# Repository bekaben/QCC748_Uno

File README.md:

# Arduino Uno Compatible Board Based on Qualcomm QCC748 SOM

<br>

<br>

This is a custom Arduino Uno-compatible board built around the Qualcomm QCC748 System-on-Module (SOM). This repository contains the full schematic, PCB layout, and supporting documentation for the board design.

## 🔧 Overview

This project implements an Arduino Uno form-factor development board using the Qualcomm QCC748 SOM as the core processing module. The design maintains compatibility with the Arduino Uno pinout while leveraging the QCC748's capabilities for enhanced wireless connectivity and processing performance. In addition, the board includes a speaker, microphone, and MicroSD card interface.

## Key Goals

\- ✅ Arduino Uno R3 mechanical footprint compatibility

\- ✅ Standard Arduino header pinout

\- ✅ USB programming interface

\- ✅ Power supply regulation (5V / 3.3V)

\- ✅ Wireless connectivity via QCC748 integrated Wifi and Bluetooth

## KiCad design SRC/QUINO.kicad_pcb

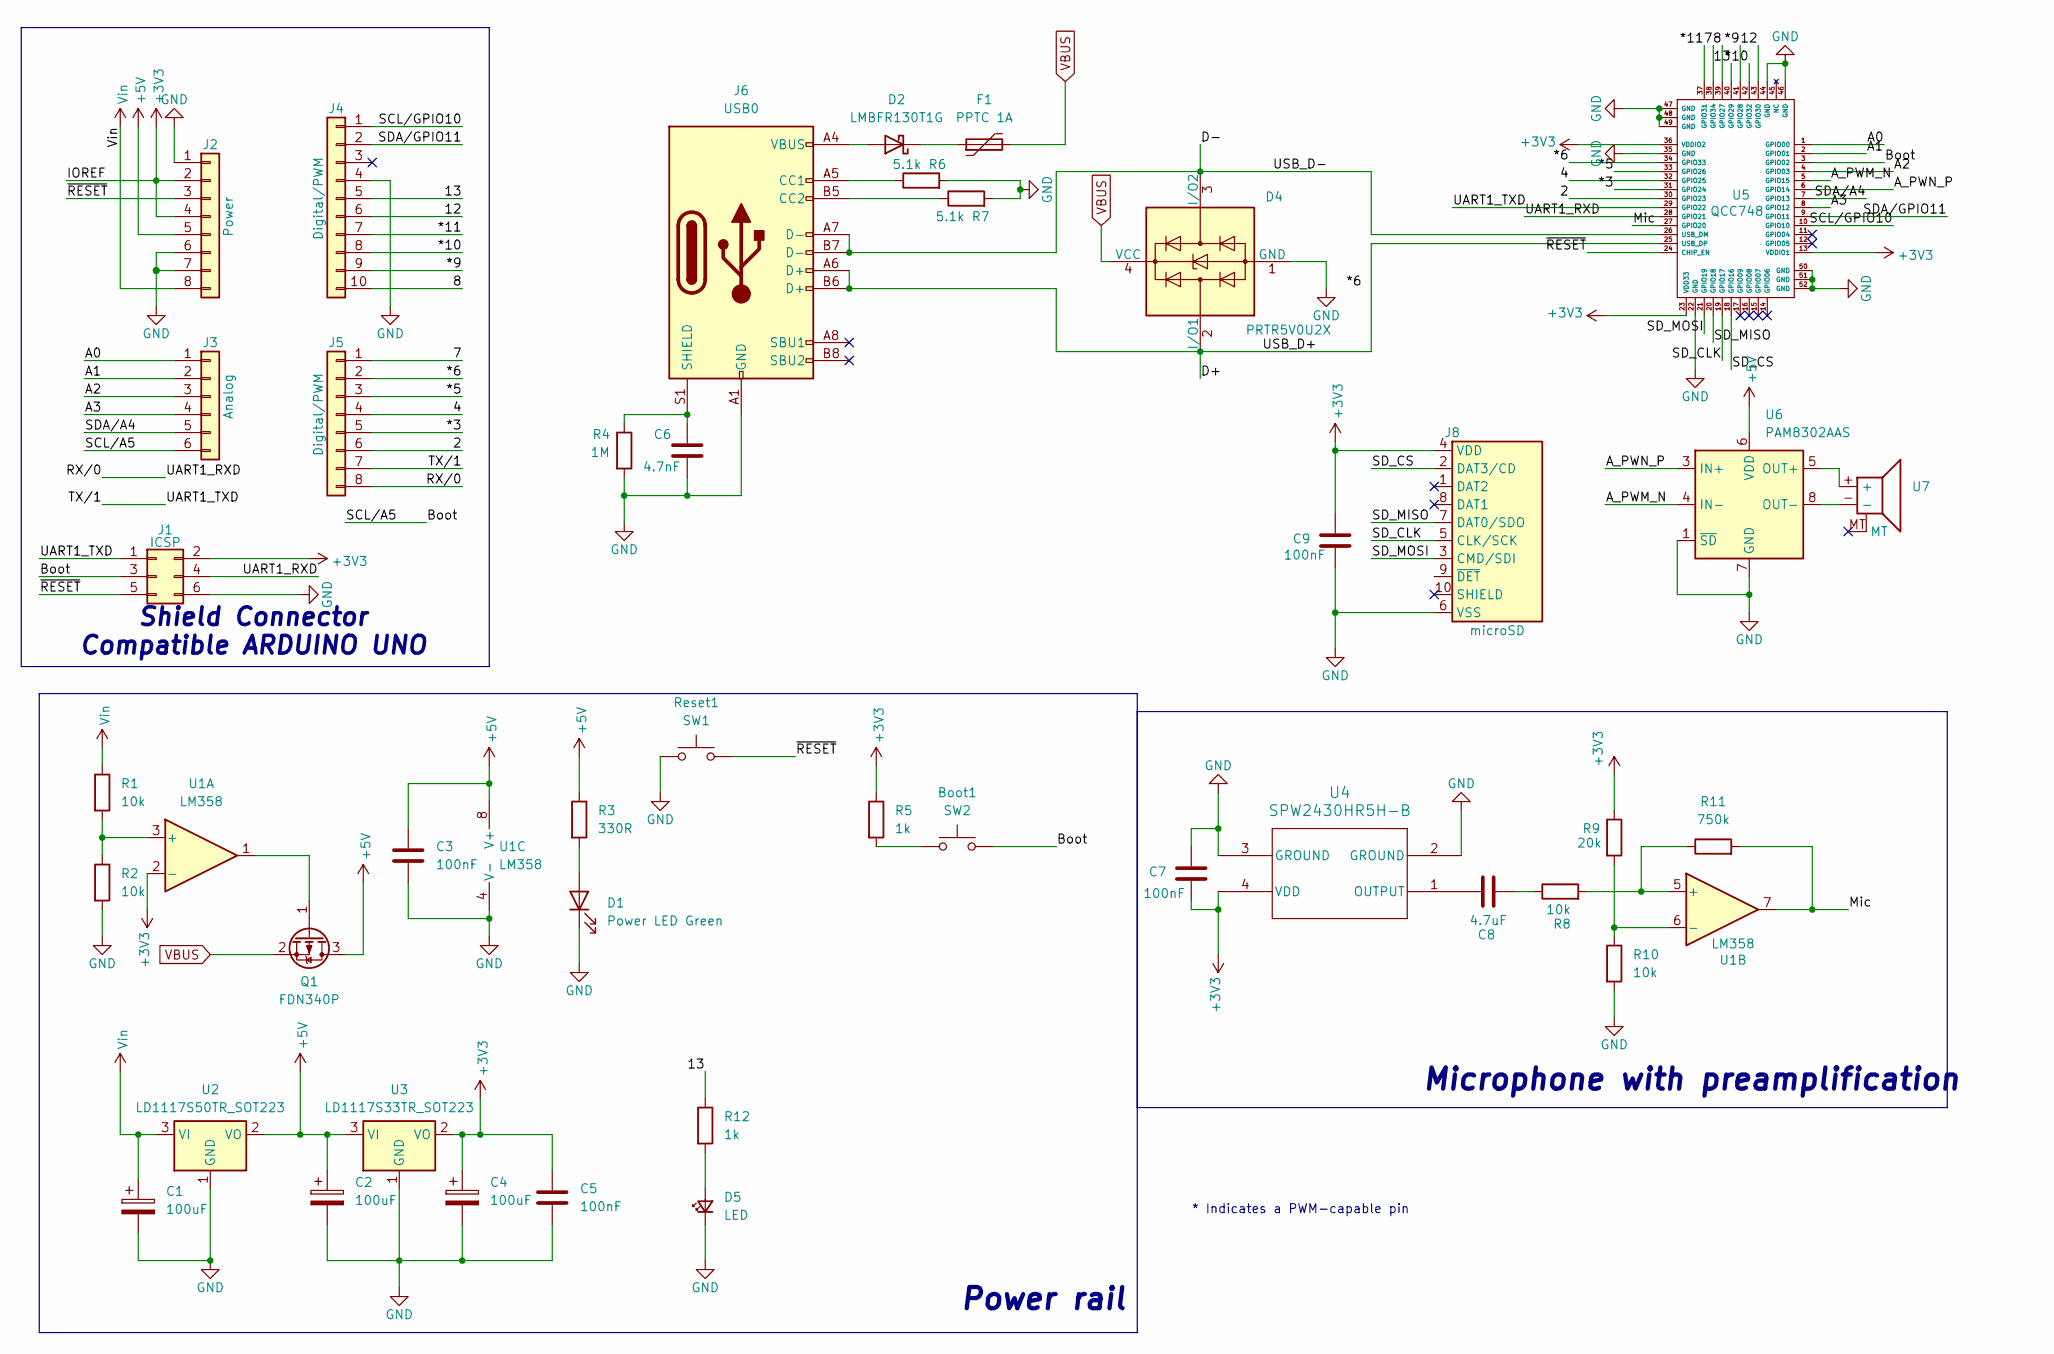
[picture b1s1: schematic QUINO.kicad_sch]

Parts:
Boot1: SW2; SW_Push_1P1T_XKB_TS-1187A
C1, C2, C4: 100uF; CP_Elec_4x3.9
C3, C5, C7, C9: 100nF; C_0402_1005Metric
C6: 4.7nF; C_0402_1005Metric
C8: 4.7uF; C_0402_1005Metric
D1: Power LED Green; LED_0402_1005Metric
D2: LMBFR130T1G; D_SOD-123
D4: PRTR5V0U2X; SOT-143
D5: LED; LED_0402_1005Metric
F1: PPTC 1A; Fuse_1206_3216Metric
J1: ICSP; PinHeader_2x03_P2.54mm_Vertical
J2: Power; PinSocket_1x08_P2.54mm_Vertical
J3: Analog; PinSocket_1x06_P2.54mm_Vertical
J4: Digital/PWM; PinSocket_1x10_P2.54mm_Vertical
J5: Digital/PWM; PinSocket_1x08_P2.54mm_Vertical
J6: USB0; USB_C_Receptacle_GCT_USB4105-xx-A_16P_TopMnt_Horizontal
J8: microSD; microSD_External_Pin
Q1: FDN340P; SOT-23
R1, R2, R8, R10: 10k; R_0402_1005Metric
R3: 330R; R_0402_1005Metric
R4: 1M; R_0402_1005Metric
R5, R12: 1k; R_0402_1005Metric
R6, R7: 5.1k; R_0402_1005Metric
R9: 20k; R_0402_1005Metric
R11: 750k; R_0402_1005Metric
Reset1: SW1; SW_Push_1P1T_XKB_TS-1187A
U1: LM358; TSSOP-8_3x3mm_P0.65mm
U2: LD1117S50TR_SOT223; SOT-223-3_TabPin2
U3: LD1117S33TR_SOT223; SOT-223-3_TabPin2
U4: SPW2430HR5H-B; SPW2430HR5H-B_KNO
U5: QCC748; QCC744M2LGM52MT010AA
U6: PAM8302AAS; MSOP-8_3x3mm_P0.65mm
U7: AD7504_SPK

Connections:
+3V3: C4.1, C5.1, C7.2, C9.1, J1.2, J2.2, J2.4, J8.4 (VDD), R5.1, R9.1, U1.2 (-), U3.2 (VO), U4.4 (VDD), U5.13 (VDDIO1), U5.23 (VDD33), U5.36 (VDDIO2)
+5V: C2.1, C3.1, J2.5, Q1.3 (D), R3.1, U1.8 (V+), U2.2 (VO), U3.3 (VI), U6.6 (VDD)
/2: J5.6, U5.30 (GPIO23)
/4: J5.4, U5.32 (GPIO25)
/7: J5.1, U5.38 (GPIO34)
/8: J4.10, U5.39 (GPIO27)
/12: J4.6, U5.43 (GPIO30)
/13: J4.5, R12.1, U5.40 (GPIO29)
/*3: J5.5, U5.31 (GPIO24)
/*5: J5.3, U5.33 (GPIO26)
/*6: J5.2, U5.34 (GPIO33)
/*9: J4.9, U5.41 (GPIO28)
/*10: J4.8, U5.42 (GPIO32)
/*11: J4.7, U5.37 (GPIO31)
/A0: J3.1, U5.1 (GPIO00)
/A1: J3.2, U5.2 (GPIO01)
/A2: J3.3, U5.4 (GPIO03)
/A3: J3.4, U5.8 (GPIO12)
/A_PWM_N: U5.5 (GPIO15), U6.4 (IN-)
/A_PWN_P: U5.6 (GPIO14), U6.3 (IN+)
/Boot: Boot1.2, J1.3, J3.6, U5.3 (GPIO02)
/D+: D4.2 (I/O1), J6.A6 (D+), J6.B6 (D+), U5.25 (USB_DP)
/D-: D4.3 (I/O2), J6.A7 (D-), J6.B7 (D-), U5.26 (USB_DM)
/Mic: R11.2, U1.7, U5.27 (GPIO20)
/RX/0: J1.4, J5.8, U5.28 (GPIO21)
/SCL/GPIO10: J4.1, U5.10 (GPIO10)
/SDA/A4: J3.5, U5.7 (GPIO13)
/SDA/GPIO11: J4.2, U5.9 (GPIO11)
/SD_CLK: J8.5 (CLK/SCK), U5.19 (GPIO17)
/SD_CS: J8.2 (DAT3/CD), U5.18 (GPIO16)
/SD_MISO: J8.7 (DAT0/SDO), U5.20 (GPIO18)
/SD_MOSI: J8.3 (CMD/SDI), U5.21 (GPIO19)
/TX/1: J1.1, J5.7, U5.29 (GPIO22)
/~RESET: J1.5, J2.3, Reset1.2, U5.24 (CHIP_EN)
GND: C1.2, C2.2, C3.2, C4.2, C5.2, C6.2, C7.1, C9.2, D1.1 (K), D4.1 (GND), D5.1 (K), J1.6, J2.1, J2.6, J2.7, J4.4, J6.A1 (GND), J6.A12 (GND), J6.B1 (GND), J6.B12 (GND), J8.6 (VSS), R2.2, R4.2, R6.2, R7.2, R10.2, Reset1.1, U1.4 (V-), U2.1 (GND), U3.1 (GND), U4.2 (GROUND), U4.3 (GROUND), U5.22 (GND), U5.35 (GND), U5.44 (GND), U5.46 (GND), U5.47 (GND), U5.48 (GND), U5.49 (GND), U5.50 (GND), U5.51 (GND), U5.52 (GND), U6.1 (~SD), U6.7 (GND); also elsewhere on the board
unnamed: Boot1.1, R5.2
unnamed: C8.2, R8.1
unnamed: D1.2 (A), R3.2
unnamed: D2.2 (A), J6.A4 (VBUS), J6.A9 (VBUS), J6.B4 (VBUS), J6.B9 (VBUS)
unnamed: D2.1 (K), F1.1
unnamed: D5.2 (A), R12.2
unnamed: J6.A5 (CC1), R6.1
unnamed: J6.B5 (CC2), R7.1
unnamed: C6.1, J6.S1 (SHIELD), R4.1
unnamed: Q1.1 (G), U1.1
unnamed: R1.2, R2.1, U1.3 (+)
unnamed: R8.2, R11.1, U1.5 (+)
unnamed: R9.2, R10.1, U1.6 (-)
unnamed: C8.1, U4.1 (OUTPUT)
unnamed: U6.5 (OUT+), U7.+
unnamed: U6.8 (OUT-), U7.-
VBUS: D4.4 (VCC), F1.2, Q1.2 (S); also elsewhere on the board
Vin: C1.1, J2.8, R1.1, U2.3 (VI); also elsewhere on the board

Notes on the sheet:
Shield Connector Compatible ARDUINO UNO
Microphone with preamplification
* Indicates a PWM-capable pin
Power rail

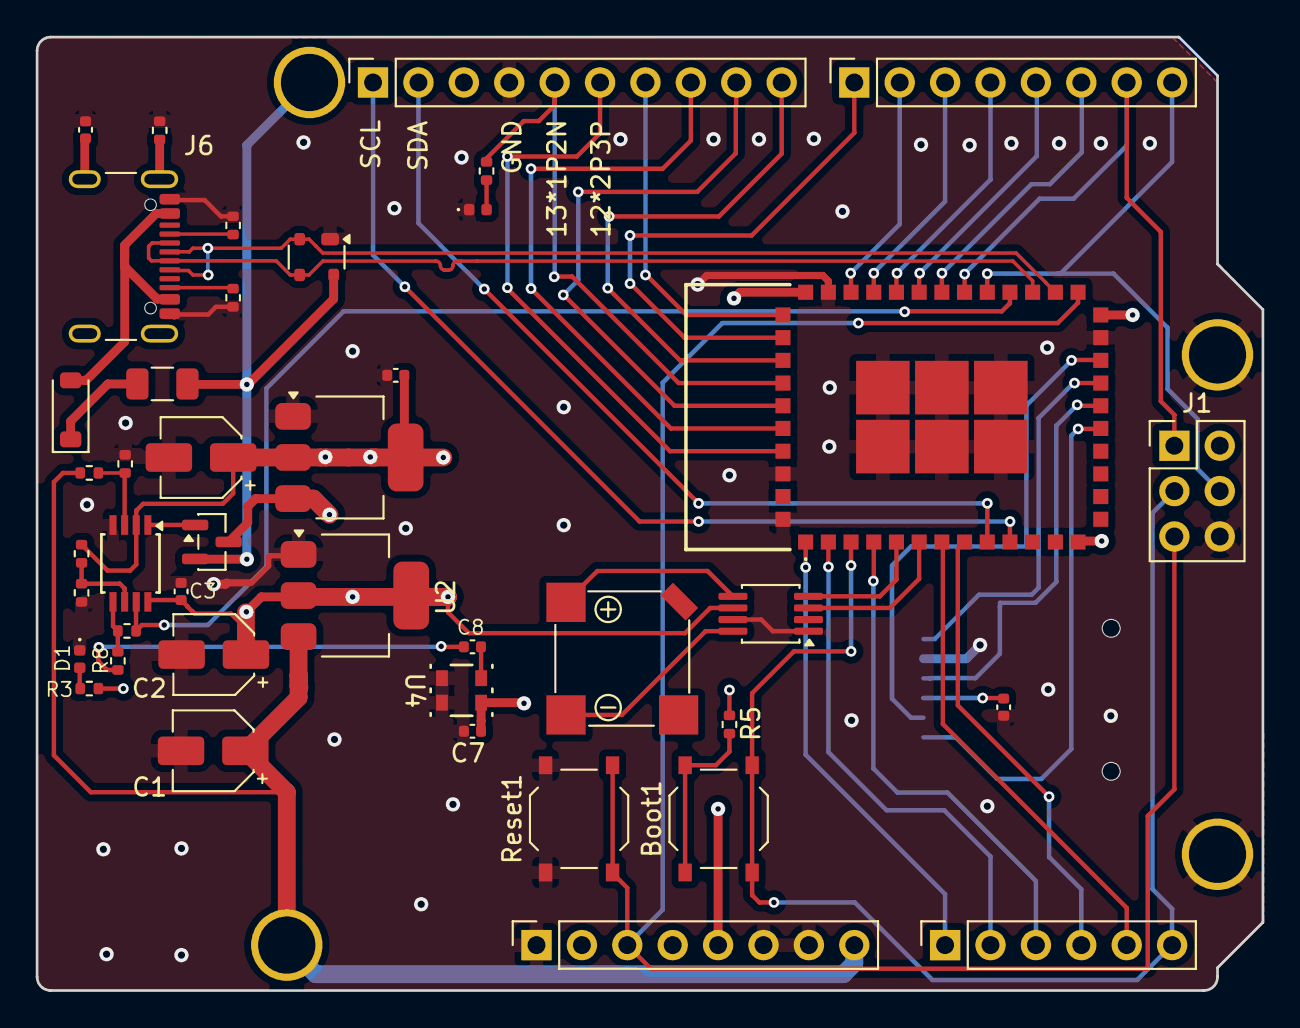
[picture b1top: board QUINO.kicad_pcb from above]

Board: 4 copper layers, 68.6 x 53.3 mm, 47 parts (1 on the bottom side), 53 nets.

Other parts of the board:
MH1, MH2, MH3, MH4: MountingHole_3.2mm

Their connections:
GND: MH3.3, MH4.4; also elsewhere on the board
VBUS: MH1.2; also elsewhere on the board
Vin: MH2.1; also elsewhere on the board
